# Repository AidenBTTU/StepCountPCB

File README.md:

# StepCountPCB
Custom PCB for a step counting device with I2C and USB communication, an external crystal oscillator, and a power system with battery charging capabilities

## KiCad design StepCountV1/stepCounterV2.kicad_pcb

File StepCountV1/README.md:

The first version of this project. 

New Features: This version includes a boot switch, a BMA400 accelerometer, a micro USB connection, and pinned-out I2C communication pins for a connected Display 

Discovered Problems: The MCU being used in this project, the STM32F103C8T6 does not come with a bootloader that allows it to be flashed via USB. This rendered the original board unprogrammable in this edition.

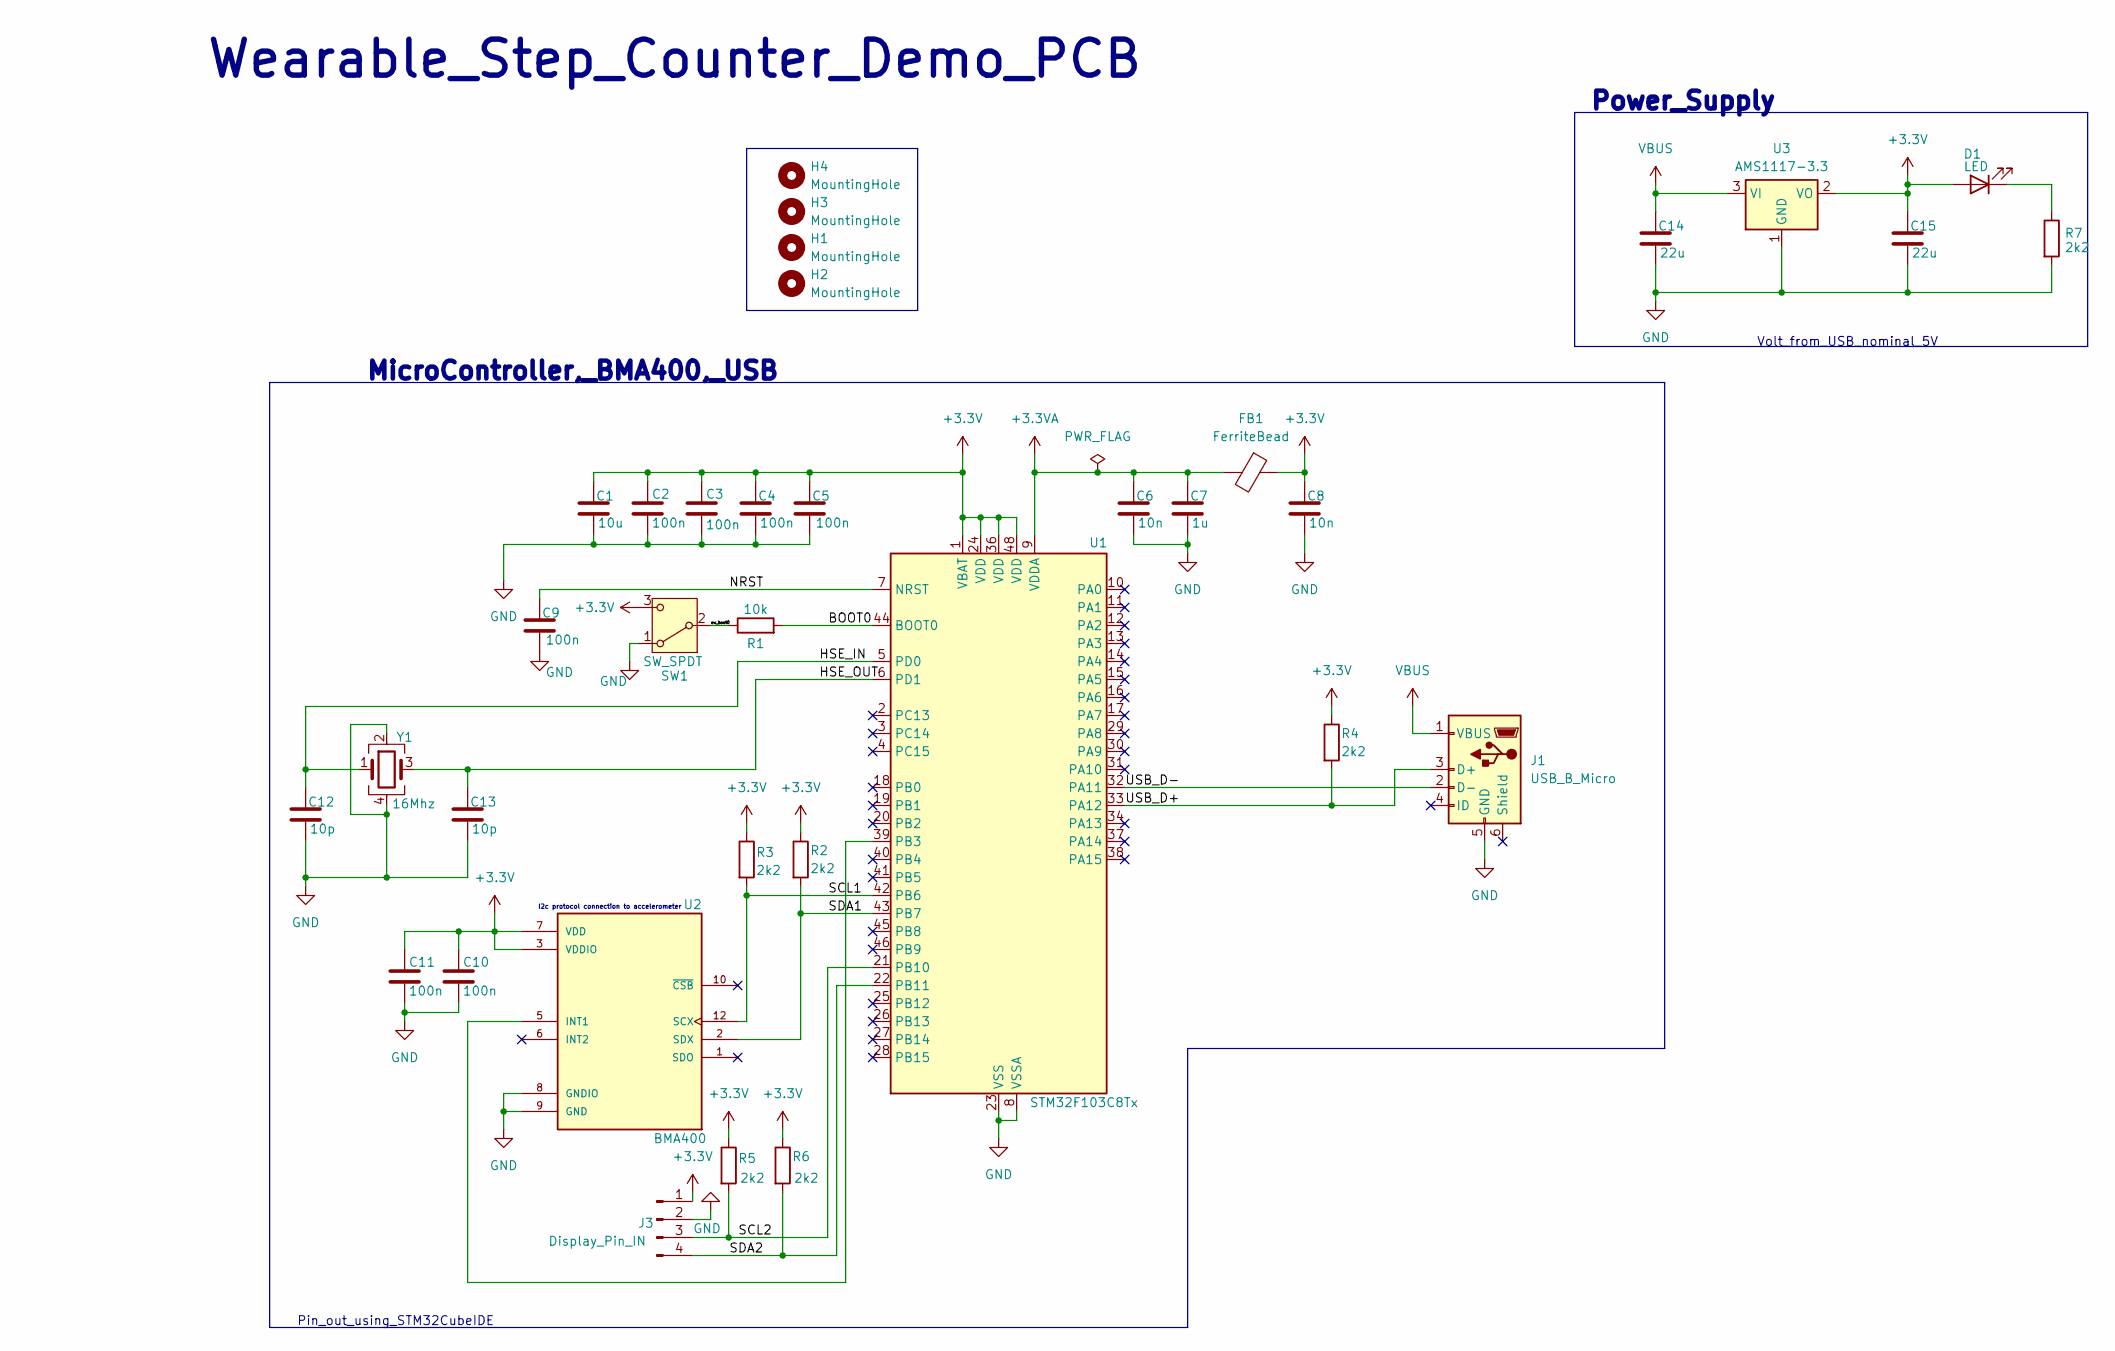
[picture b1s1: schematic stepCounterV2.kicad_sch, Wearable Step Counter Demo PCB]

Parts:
C1: 10u; C_0603_1608Metric
C2, C3, C4, C5, C9, C10, C11: 100n; C_0402_1005Metric
C6, C8: 10n; C_0402_1005Metric
C7: 1u; C_0402_1005Metric
C12, C13: 10p; C_0402_1005Metric
C14, C15: 22u; C_0805_2012Metric
D1: LED; LED_0603_1608Metric
FB1: FerriteBead; L_0603_1608Metric
H1, H2, H3, H4: MountingHole; MountingHole_2.2mm_M2
J1: USB_B_Micro; USB_Micro-B_Wuerth_629105150521
J3: Display_Pin_IN; PinSocket_1x04_P2.54mm_Vertical
R1: 10k; R_0402_1005Metric
R2, R3, R4, R5, R6, R7: 2k2; R_0402_1005Metric
SW1: SW_SPDT; SW_SPDT_PCM12
U1: STM32F103C8Tx; LQFP-48_7x7mm_P0.5mm
U2: BMA400; XDCR_BMA400
U3: AMS1117-3.3; SOT-223-3_TabPin2
Y1: 16Mhz; Crystal_SMD_3225-4Pin_3.2x2.5mm

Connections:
+3.3V: C1.1, C2.1, C3.1, C4.1, C5.1, C8.1, C10.1, C11.1, C15.1, D1.2 (A), FB1.1, J3.1, R2.1, R3.1, R4.1, R5.1, R6.1, SW1.3 (C), U1.1 (VBAT), U1.24 (VDD), U1.36 (VDD), U1.48 (VDD), U2.3 (VDDIO), U2.7 (VDD), U3.2 (VO)
+3.3VA: C6.1, C7.1, FB1.2, U1.9 (VDDA)
/ SCL1: R3.2, U1.42 (PB6), U2.12 (SCX)
/ SCL2: J3.3, R5.2, U1.21 (PB10)
/ SDA1: R2.2, U1.43 (PB7), U2.2 (SDX)
/ SDA2: J3.4, R6.2, U1.22 (PB11)
/BOOT0: R1.2, U1.44 (BOOT0)
/HSE_IN: C12.1, U1.5 (PD0), Y1.1
/HSE_OUT: C13.1, U1.6 (PD1), Y1.3
/NRST: C9.1, U1.7 (NRST)
/USB_D+: J1.3 (D+), R4.2, U1.33 (PA12)
/USB_D-: J1.2 (D-), U1.32 (PA11)
/sw_boot0: R1.1, SW1.2 (B)
GND: C1.2, C2.2, C3.2, C4.2, C5.2, C6.2, C7.2, C8.2, C9.2, C10.2, C11.2, C12.2, C13.2, C14.2, C15.2, J1.5 (GND), J3.2, R7.2, SW1.1 (A), U1.8 (VSSA), U1.23 (VSS), U1.35 (VSS), U1.47 (VSS), U2.8 (GNDIO), U2.9 (GND), U3.1 (GND), Y1.2, Y1.4
unnamed: D1.1 (K), R7.1
unnamed: U1.39 (PB3), U2.5 (INT1)
VBUS: C14.1, J1.1 (VBUS), U3.3 (VI)

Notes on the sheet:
Pin_out_using_STM32CubeIDE
Power_Supply
Volt_from_USB_nominal_5V
Wearable_Step_Counter_Demo_PCB
MicroController,_BMA400,_USB
I2c protocol connection to accelerometer

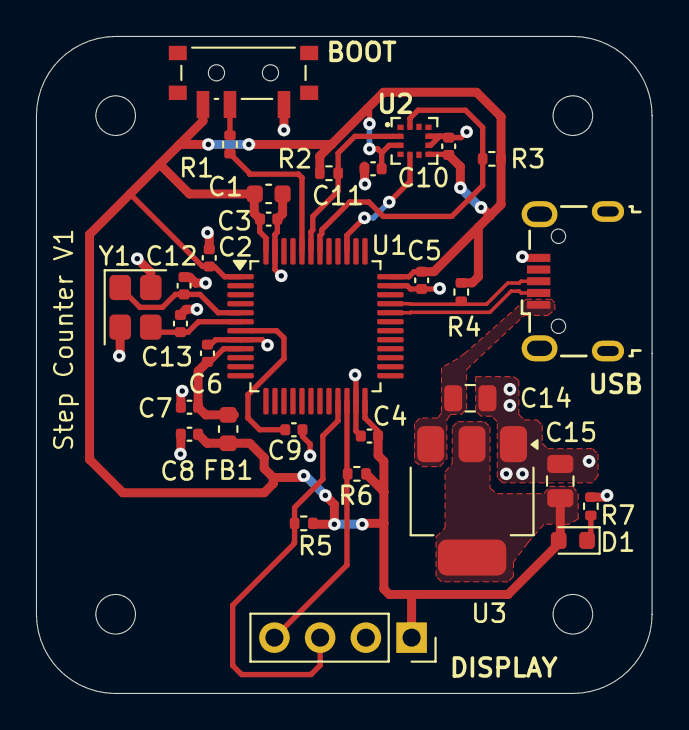
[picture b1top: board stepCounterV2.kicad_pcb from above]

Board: 2 copper layers, 34.2 x 36.5 mm, 35 parts (0 on the bottom side), 17 nets.

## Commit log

2025-08-08 Create info
2025-08-08 Update info
2025-08-08 Placement Files, Bill of Materials
2025-08-08 Rename BOM StepCounterV2 Final - stepCounterV2-JLCPCB Assembly Order.xls to StepCounterV1Placement.xls
2025-08-08 Rename stepCounterV2.kicad_pro to stepCounterV1.kicad_pro
2025-08-08 PCB files for V2
2025-08-08 Rename stepCounterV3.kicad_pro to stepCounterV2.kicad_pro
2025-08-08 BOm and Placement
2025-08-08 Rename info.md to README.md
